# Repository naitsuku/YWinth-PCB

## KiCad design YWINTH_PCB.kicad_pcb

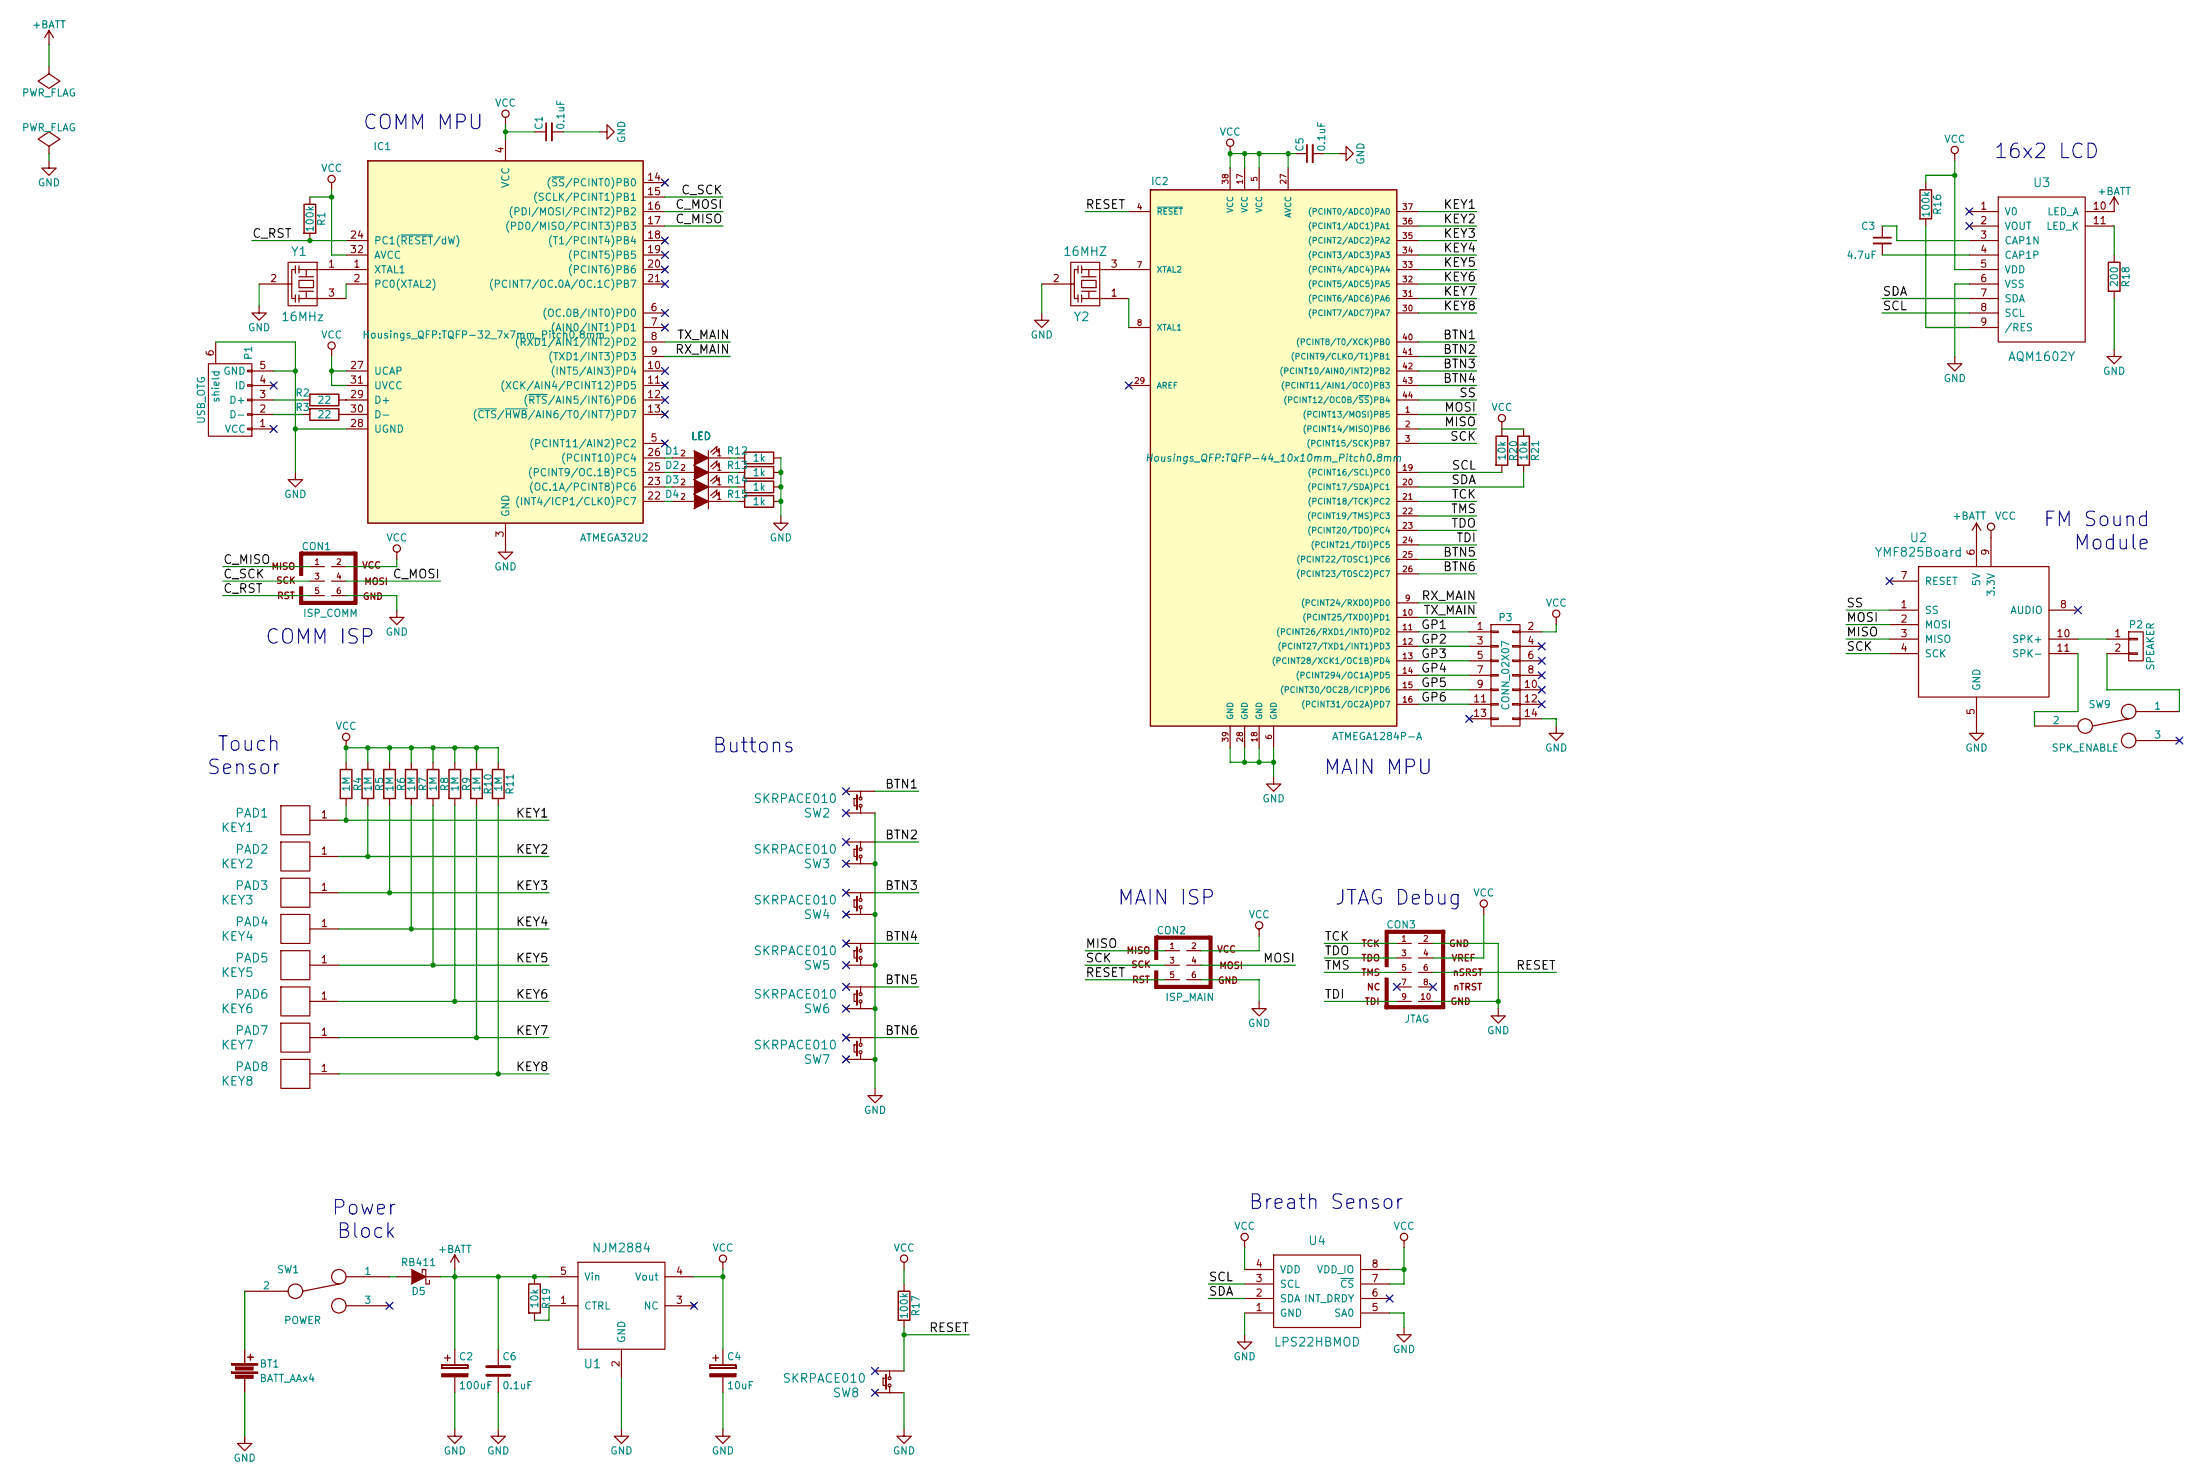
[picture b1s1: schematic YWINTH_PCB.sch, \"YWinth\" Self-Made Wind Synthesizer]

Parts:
BT1: BATT_AAx4; JST_XH_B02B-XH-A_02x2.50mm_Straight
C1, C5, C6: 0.1uF; C_0603_HandSoldering
C2: 100uF; c_elec_5x5.3
C3: 4.7uF; C_0603_HandSoldering
C4: 10uF; c_elec_5x5.3
CON1: ISP_COMM; Pin_Header_Straight_2x03
CON2: ISP_MAIN; Pin_Header_Straight_2x03
CON3: JTAG; IDC_Header_Straight_10pins
D1, D2, D3, D4: LED; LED_0603
D5: RB411; SOT-23_Handsoldering
IC1: ATMEGA32U2; TQFP-32_7x7mm_Pitch0.8mm
IC2: ATMEGA1284P-A; TQFP-44_10x10mm_Pitch0.8mm
P1: USB_OTG; ZX62R-B-5P
P2: SPEAKER; JST_XH_B02B-XH-A_02x2.50mm_Straight
P3: CONN_02X07; IDC_Header_Straight_14pins
PAD1: KEY1; TOUCHPAD_L
PAD2: KEY2; TOUCHPAD_L
PAD3: KEY3; TOUCHPAD_L
PAD4: KEY4; TOUCHPAD_L
PAD5: KEY5; TOUCHPAD_R
PAD6: KEY6; TOUCHPAD_R
PAD7: KEY7; TOUCHPAD_R
PAD8: KEY8; TOUCHPAD_R
R1, R16, R17: 100k; R_0603_HandSoldering
R2, R3: 22; R_0603_HandSoldering
R4, R5, R6, R7, R8, R9, R10, R11: 1M; R_0603_HandSoldering
R12, R13, R14, R15: 1k; R_0603_HandSoldering
R18: 200; R_0603_HandSoldering
R19, R20, R21: 10k; R_0603_HandSoldering
SW1: POWER; SK-12D01-VG4
SW2, SW3, SW4, SW5, SW6, SW7, SW8: SKRPACE010
SW9: SPK_ENABLE; SK-12D01-VG4
U1: NJM2884; SOT89-5_Housing
U2: YMF825Board; YMF825
U3: AQM1602Y; AQM1602
U4: LPS22HBMOD
Y1: 16MHz; SMD_Ceraloc
Y2: 16MHZ; SMD_Ceraloc

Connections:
+BATT: C2.1, C6.1, D5.1 (K), R19.1, U1.5 (Vin), U2.6 (5V), U3.10 (LED_A)
/BTN1: IC2.40 ((PCINT8/T0/XCK)PB0), SW2.2
/BTN2: IC2.41 ((PCINT9/CLKO/T1)PB1), SW3.2
/BTN3: IC2.42 ((PCINT10/AIN0/INT2)PB2), SW4.2
/BTN4: IC2.43 ((PCINT11/AIN1/OC0)PB3), SW5.2
/BTN5: IC2.25 ((PCINT22/TOSC1)PC6), SW6.2
/BTN6: IC2.26 ((PCINT23/TOSC2)PC7), SW7.2
/C_MISO: CON1.1, IC1.17 ((PD0/MISO/PCINT3)PB3)
/C_MOSI: CON1.4, IC1.16 ((PDI/MOSI/PCINT2)PB2)
/C_RST: CON1.5, IC1.24 (PC1(~RESET~/dW)), R1.2
/C_SCK: CON1.3, IC1.15 ((SCLK/PCINT1)PB1)
/GP1: IC2.11 ((PCINT26/RXD1/INT0)PD2), P3.1
/GP2: IC2.12 ((PCINT27/TXD1/INT1)PD3), P3.3
/GP3: IC2.13 ((PCINT28/XCK1/OC1B)PD4), P3.5
/GP4: IC2.14 ((PCINT294/OC1A)PD5), P3.7
/GP5: IC2.15 ((PCINT30/OC2B/ICP)PD6), P3.9
/GP6: IC2.16 ((PCINT31/OC2A)PD7), P3.11
/KEY1: IC2.37 ((PCINT0/ADC0)PA0), PAD1.1, R4.2
/KEY2: IC2.36 ((PCINT1/ADC1)PA1), PAD2.1, R5.2
/KEY3: IC2.35 ((PCINT2/ADC2)PA2), PAD3.1, R6.2
/KEY4: IC2.34 ((PCINT3/ADC3)PA3), PAD4.1, R7.2
/KEY5: IC2.33 ((PCINT4/ADC4)PA4), PAD5.1, R8.2
/KEY6: IC2.32 ((PCINT5/ADC5)PA5), PAD6.1, R9.2
/KEY7: IC2.31 ((PCINT6/ADC6)PA6), PAD7.1, R10.2
/KEY8: IC2.30 ((PCINT7/ADC7)PA7), PAD8.1, R11.2
/MISO: CON2.1, IC2.2 ((PCINT14/MISO)PB6), U2.3 (MISO)
/MOSI: CON2.4, IC2.1 ((PCINT13/MOSI)PB5), U2.2 (MOSI)
/RESET: CON2.5, CON3.6, IC2.4 (~RESET), R17.2, SW8.2
/RX_MAIN: IC1.9 ((TXD1/INT3)PD3), IC2.9 ((PCINT24/RXD0)PD0)
/SCK: CON2.3, IC2.3 ((PCINT15/SCK)PB7), U2.4 (SCK)
/SCL: IC2.19 ((PCINT16/SCL)PC0), R20.2, U3.8 (SCL), U4.3 (SCL)
/SDA: IC2.20 ((PCINT17/SDA)PC1), R21.2, U3.7 (SDA), U4.2 (SDA)
/SS: IC2.44 ((PCINT12/OC0B/~SS~)PB4), U2.1 (SS)
/TCK: CON3.1, IC2.21 ((PCINT18/TCK)PC2)
/TDI: CON3.9, IC2.24 ((PCINT21/TDI)PC5)
/TDO: CON3.3, IC2.23 ((PCINT20/TDO)PC4)
/TMS: CON3.5, IC2.22 ((PCINT19/TMS)PC3)
/TX_MAIN: IC1.8 ((RXD1/AIN1/INT2)PD2), IC2.10 ((PCINT25/TXD0)PD1)
GND: BT1.2, C1.2, C2.2, C4.2, C5.2, C6.2, CON1.6, CON2.6, CON3.2, CON3.10, IC1.3 (GND), IC1.28 (UGND), IC2.6 (GND), IC2.18 (GND), IC2.28 (GND), IC2.39 (GND), P1.5 (GND), P1.6 (shield), P3.14, R12.1, R13.1, R14.1, R15.1, R18.2, SW2.4, SW3.4, SW4.4, SW5.4, SW6.4, SW7.4, SW8.4, U1.2 (GND), U2.5 (GND), U3.6 (VSS), U4.1 (GND), U4.5 (SA0), Y1.2 (GND), Y2.2 (GND)
unnamed: BT1.1, SW1.2
unnamed: C3.1, U3.3 (CAP1N)
unnamed: C3.2, U3.4 (CAP1P)
unnamed: D1.1 (K), R12.2
unnamed: D1.2 (A), IC1.26 ((PCINT10)PC4)
unnamed: D2.1 (K), R13.2
unnamed: D2.2 (A), IC1.25 ((PCINT9/OC.1B)PC5)
unnamed: D3.1 (K), R14.2
unnamed: D3.2 (A), IC1.23 ((OC.1A/PCINT8)PC6)
unnamed: D4.1 (K), R15.2
unnamed: D4.2 (A), IC1.22 ((INT4/ICP1/CLK0)PC7)
unnamed: D5.2 (A), SW1.1
unnamed: IC1.1 (XTAL1), Y1.1 (IN)
unnamed: IC1.2 (PC0(XTAL2)), Y1.3 (OUT)
unnamed: IC1.29 (D+), R2.1
unnamed: IC1.30 (D-), R3.1
unnamed: IC2.7 (XTAL2), Y2.3 (OUT)
unnamed: IC2.8 (XTAL1), Y2.1 (IN)
unnamed: P1.2 (D-), R3.2
unnamed: P1.3 (D+), R2.2
unnamed: P2.1, U2.10 (SPK+)
unnamed: P2.2, SW9.1
unnamed: R16.2, U3.9 (/RES)
unnamed: R18.1, U3.11 (LED_K)
unnamed: R19.2, U1.1 (CTRL)
unnamed: SW9.2, U2.11 (SPK-)
VCC: C1.1, C4.1, C5.1, CON1.2, CON2.2, CON3.4, IC1.4 (VCC), IC1.27 (UCAP), IC1.31 (UVCC), IC1.32 (AVCC), IC2.5 (VCC), IC2.17 (VCC), IC2.27 (AVCC), IC2.38 (VCC), P3.2, R1.1, R4.1, R5.1, R6.1, R7.1, R8.1, R9.1, R10.1, R11.1, R16.1, R17.1, R20.1, R21.1, U1.4 (Vout), U2.9 (3.3V), U3.5 (VDD), U4.4 (VDD), U4.7 (~CS), U4.8 (VDD_IO)

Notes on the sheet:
JTAG Debug
Touch Sensor
MAIN MPU
COMM MPU
16x2 LCD
FM Sound Module
Breath Sensor
Power Block
MAIN ISP
COMM ISP
Buttons

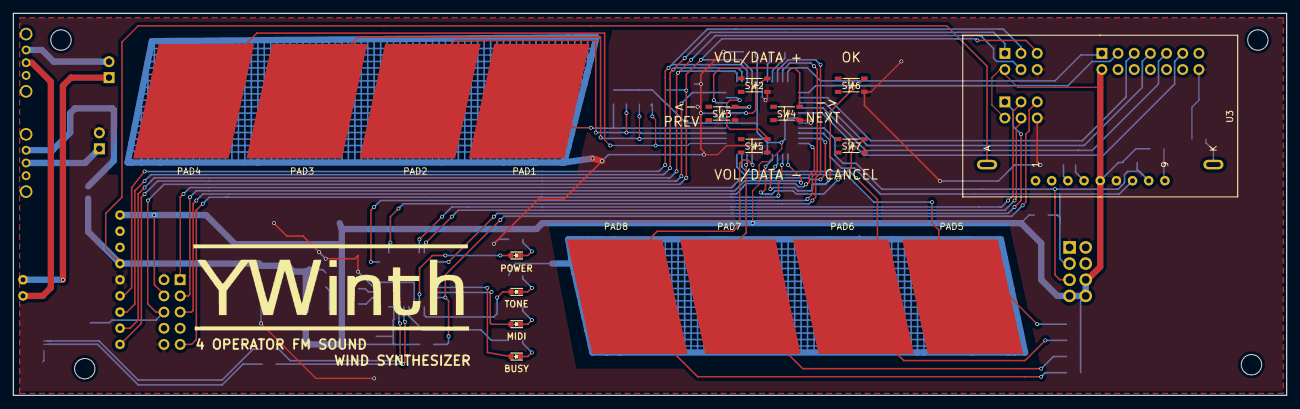
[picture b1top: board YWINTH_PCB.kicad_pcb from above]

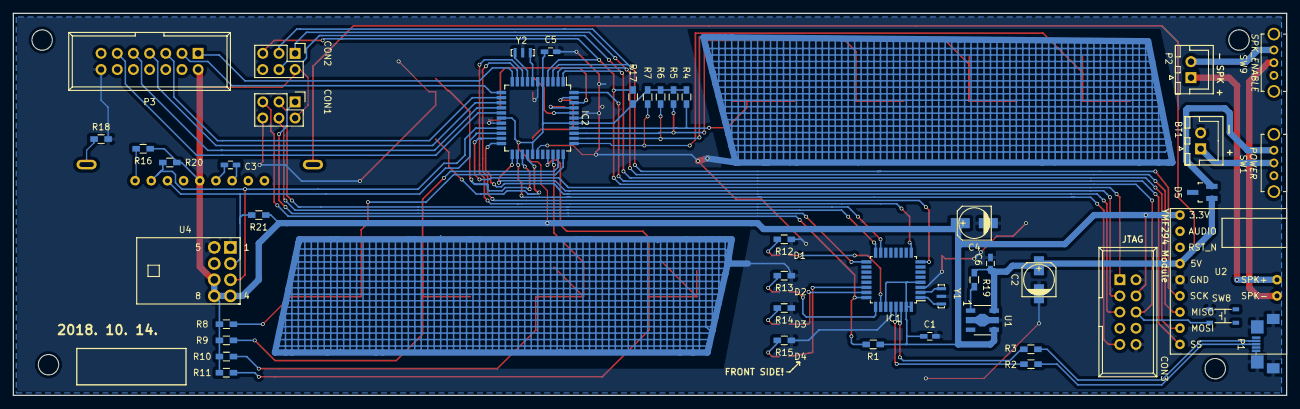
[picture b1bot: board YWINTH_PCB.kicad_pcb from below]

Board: 2 copper layers, 200.0 x 60.0 mm, 64 parts (45 on the bottom side), 66 nets.

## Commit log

2021-01-09 YWinth Schematic&PCB Kicad Project Datas.
